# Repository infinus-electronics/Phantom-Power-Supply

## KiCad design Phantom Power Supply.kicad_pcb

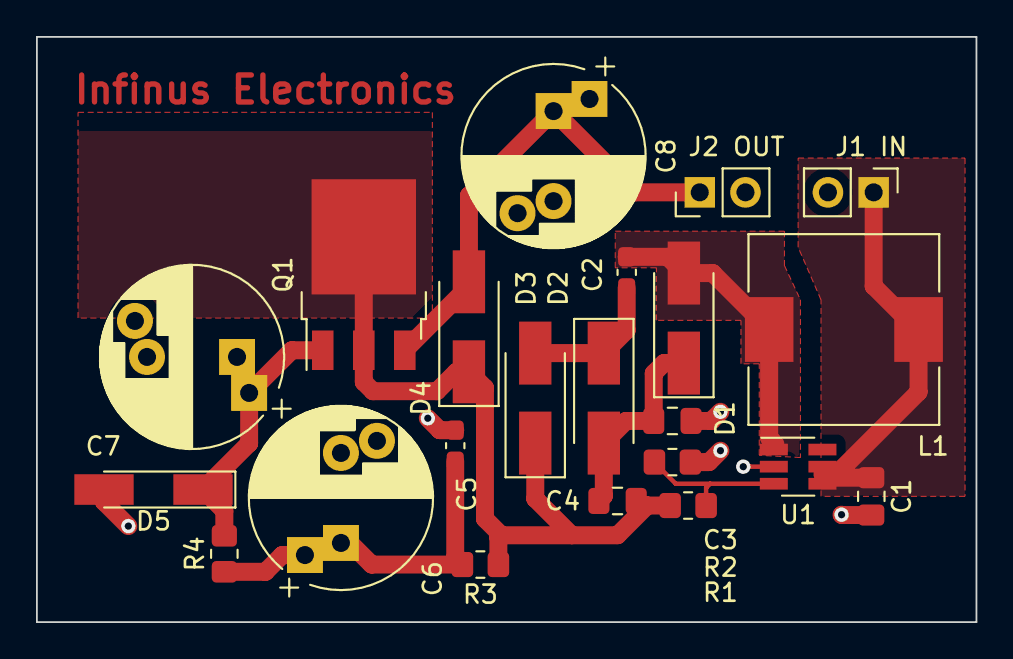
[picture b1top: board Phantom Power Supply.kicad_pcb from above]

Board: 2 copper layers, 52.2 x 32.5 mm, 22 parts (0 on the bottom side), 10 nets.

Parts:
C1: 22u; C_0805_2012Metric_Pad1.18x1.45mm_HandSolder
C2, C5: 1u; C_0603_1608Metric_Pad1.08x0.95mm_HandSolder
C3, C4: 4.7u; C_0805_2012Metric_Pad1.18x1.45mm_HandSolder
C6, C7, C8: C_Polarized; CP_Radial_D10.0mm_P5.00mm_P7.50mm
D1, D2, D3: D_Schottky; D_SMA_Handsoldering
D4: D; D_SMA_Handsoldering
D5: D_Zener; D_MiniMELF_Handsoldering
J1 IN, J2 OUT: Conn_01x02_Male; PinHeader_1x02_P2.54mm_Vertical
L1: L; L_10.4x10.4_H4.8
Q1: Q_NPN_BCEC; TO-252-3_TabPin4
R1, R2, R3, R4: R; R_0805_2012Metric_Pad1.20x1.40mm_HandSolder
U1: SB6286; SOT-23-6_Handsoldering

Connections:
+48V: C8.1, D4.2 (A), J2 OUT.1, Q1.3 (E)
GND: C1.2, C3.1, C5.2, C6.2, C7.2, C8.2, D5.2 (A), J1 IN.2, J2 OUT.2, R2.2, U1.2 (GND)
unnamed: C2.1, D1.2 (A), L1.2, U1.1 (SW)
unnamed: C2.2, D2.1 (K), D3.2 (A)
unnamed: C3.2, C4.1, D1.1 (K), D2.2 (A)
unnamed: C4.2, D3.1 (K), D4.1 (K), Q1.2 (C), Q1.4 (C), R1.1, R3.1
unnamed: C5.1, C6.1, R3.2, R4.1
unnamed: C7.1, D5.1 (K), Q1.1 (B), R4.2
unnamed: R1.2, R2.1, U1.3 (FB)
VDD: C1.1, J1 IN.1, L1.1, U1.4 (EN), U1.5 (VIN)

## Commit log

2022-02-25 pdfs
2022-02-25 backups
